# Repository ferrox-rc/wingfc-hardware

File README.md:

# WingFC Hardware Carrier Board

Official hardware carrier board design, schematics, PCB layout, and mechanical CAD for the **WingFC** open-source flight controller ecosystem.

Engineered specifically for sub-250g FPV flying wings, acrobatic wings, and compact autonomous UAVs, this carrier board hosts the **Seeed Studio XIAO nRF52840 Sense Plus** and breaks out all actuation channels, serial links, and power regulation onto an ultra-compact footprint.

---

## 3D Board Visualizations

| Isometric 3D View | Top View | Bottom View |
| :---: | :---: | :---: |
|  |  |  |

---

## Key Hardware Features

- **Standard 25.5 × 25.5 mm Whoop Mounting Pattern:** Fits standard micro-quad and fixed-wing carrier bays with 4× M2 mounting holes (`H1`–`H4`).
- **Ultra-Compact Profile:** Only **32.0 mm wide × 33.2 mm long**, minimizing mass and fuselage cavity requirements.
- **Edge-Mounted North-Facing USB-C Port:**
  - MCU rotated so the USB-C receptacle faces forward into free air.
  - Dedicated $10.0\,\text{mm} \times 0.8\,\text{mm}$ recessed access notch ensures standard USB-C cables plug in flush without mechanical collision.
- **10 Actuator Channels (2 ESCs + 8 Servos):**
  - **6 Primary Channels (`ESC1`, `ESC2`, `S1`..`S4`):** Standard 2.54 mm pitch vertical pin headers (Signal / +5V / GND) nestled directly between lower mounting screws `H3` and `H4`.
  - **4 Auxiliary Channels (`S5`..`S8`):** Compact 1.27 mm pitch horizontal pin headers located in the East bay for advanced airframe functions (flaps, pan/tilt gimbals, landing gear, payload drop).
- **Outward-Facing JST-SH Quick-Connect Sockets:**
  - **RC Receiver (`J_RC`):** 4-pin horizontal JST-SH on the West flank (5V, GND, UARTE0 TX/RX for CRSF/ELRS/iBus).
  - **GPS & Navigation (`J_GPS`):** 6-pin horizontal JST-SH on the East flank (5V, GND, UARTE1 TX/RX for NMEA GPS, TWISPI1 SDA/SCL for external compass).
- **High-Efficiency 5V / 2A Synchronous BEC:**
  - Monolithic Power Systems **MP2315** high-efficiency step-down buck regulator on the bottom layer.
  - Supports 2S to 4S LiPo input voltages (up to 24V).
  - High-current Bourns SRN4018 3.3µH shielded power inductor.
- **Comprehensive Power & Brownout Protection:**
  - **VBAT TVS (`D3`):** Littelfuse SMAJ24A (400W) TVS diode across battery input pads.
  - **+5V TVS (`D4`):** Littelfuse SMAJ5.0A (400W) TVS diode across the servo rail.
  - **Servo Surge Buffer (`C_BULK`):** 100µF 1206 low-ESR ceramic capacitor absorbs motor/servo inductive spikes.
  - **MCU Brownout Hold-Up (`C8` + `D1`):** Diodes Inc B0520W Schottky diode and 22µF 0805 capacitor buffer the MCU 5V rail (`+5V_MCU`) against aerodynamic stall current spikes.
  - **ESC BEC Isolation (`JP1`, `JP2`):** Solder jumpers to disconnect +5V from ESC1 and ESC2 pins, preventing back-feeding into the onboard regulator.
- **Integrated High-Precision Barometer:**
  - Onboard Infineon **DPS310** 24-bit barometric pressure sensor on the secondary I2C bus (`TWISPI1`).
  - Enables sub-meter altitude hold and autonomous vertical Kalman filtering.
- **Antenna Keepout Zone:**
  - Complete copper-free zone across all 4 layers under the South antenna portion of the XIAO module.
- **Breakout & Testability:**
  - SWD test pads (`TP1`..`TP5`): SWCLK, SWDIO, RST, GND, 3V3.
  - Spare GPIO breakout pads (`TP6`..`TP8`): D17, D18, D19.
  - 11:1 precision resistor divider (100kΩ / 10kΩ + 100nF filtering) connected to SAADC `AIN7` (`D16` / `P0.31`) for LiPo pack telemetry.

---

## Pinout & Electrical Allocation

| Header / Pin | Label | nRF52840 Pin | Peripheral | Function |
| :--- | :--- | :--- | :--- | :--- |
| **ESC 1** | `ESC1` | `P0.02` (`D0`) | `PWM0` Ch 0 | Motor 1 (DShot / PWM) |
| **ESC 2** | `ESC2` | `P0.03` (`D1`) | `PWM0` Ch 1 | Motor 2 / Differential Thrust |
| **Servo 1** | `S1` | `P0.04` (`D2`) | `PWM1` Ch 0 | Elevon Left / Aileron |
| **Servo 2** | `S2` | `P0.05` (`D3`) | `PWM1` Ch 1 | Elevon Right / Elevator |
| **Servo 3** | `S3` | `P0.28` (`D4`) | `PWM1` Ch 2 | Rudder / V-Tail |
| **Servo 4** | `S4` | `P0.29` (`D5`) | `PWM1` Ch 3 | Flap Left / Aux |
| **Servo 5** | `S5` | `P0.17` (`D11`)| `PWM2` Ch 0 | Aux / Pan Servo |
| **Servo 6** | `S6` | `P0.18` (`D12`)| `PWM2` Ch 1 | Flap Right / Tilt Servo |
| **Servo 7** | `S7` | `P0.19` (`D13`)| `PWM2` Ch 2 | Aux / Gear Retract |
| **Servo 8** | `S8` | `P0.20` (`D14`)| `PWM2` Ch 3 | Payload Drop / Aux |
| **RC Connector** | `J_RC` | `P1.11` / `P1.12` | `UARTE0` | CRSF / ELRS @ 420k or iBus @ 115.2k |
| **GPS Serial** | `J_GPS` | `P0.09` / `P0.10` | `UARTE1` | NMEA GPS @ 115.2k |
| **External I2C**| `J_GPS` | `P0.15` / `P0.16` | `TWISPI1` | QMC5883L Compass / Ext. Sensors |
| **Battery ADC** | `VBAT_SENSE`| `P0.31` (`D16`)| `SAADC` AIN7 | 11:1 LiPo Voltage Sensing |

---

## KiCad Project Structure

The KiCad project is located in [`kicad/`](kicad/):
- `WingFC.kicad_pro`: KiCad project management file.
- `WingFC.kicad_sch`: Master schematic (includes onboard power supply, filtering, and breakout nets).
- `WingFC.kicad_pcb`: 4-layer PCB layout with dedicated power planes and signal routing.
- `build_pcb.py`: Automated layout generator and validation script.
- `footprints/`: Self-contained project footprint libraries.

---

## Compatible Firmware

This carrier board is fully supported by the **WingFC-rs** bare-metal Rust flight controller firmware:
👉 **[ferrox-rc/wingfc-rs](https://github.com/ferrox-rc/wingfc-rs)**

---

## License

Hardware design files, schematics, PCB layouts, and documentation are licensed under the [MIT License](LICENSE).

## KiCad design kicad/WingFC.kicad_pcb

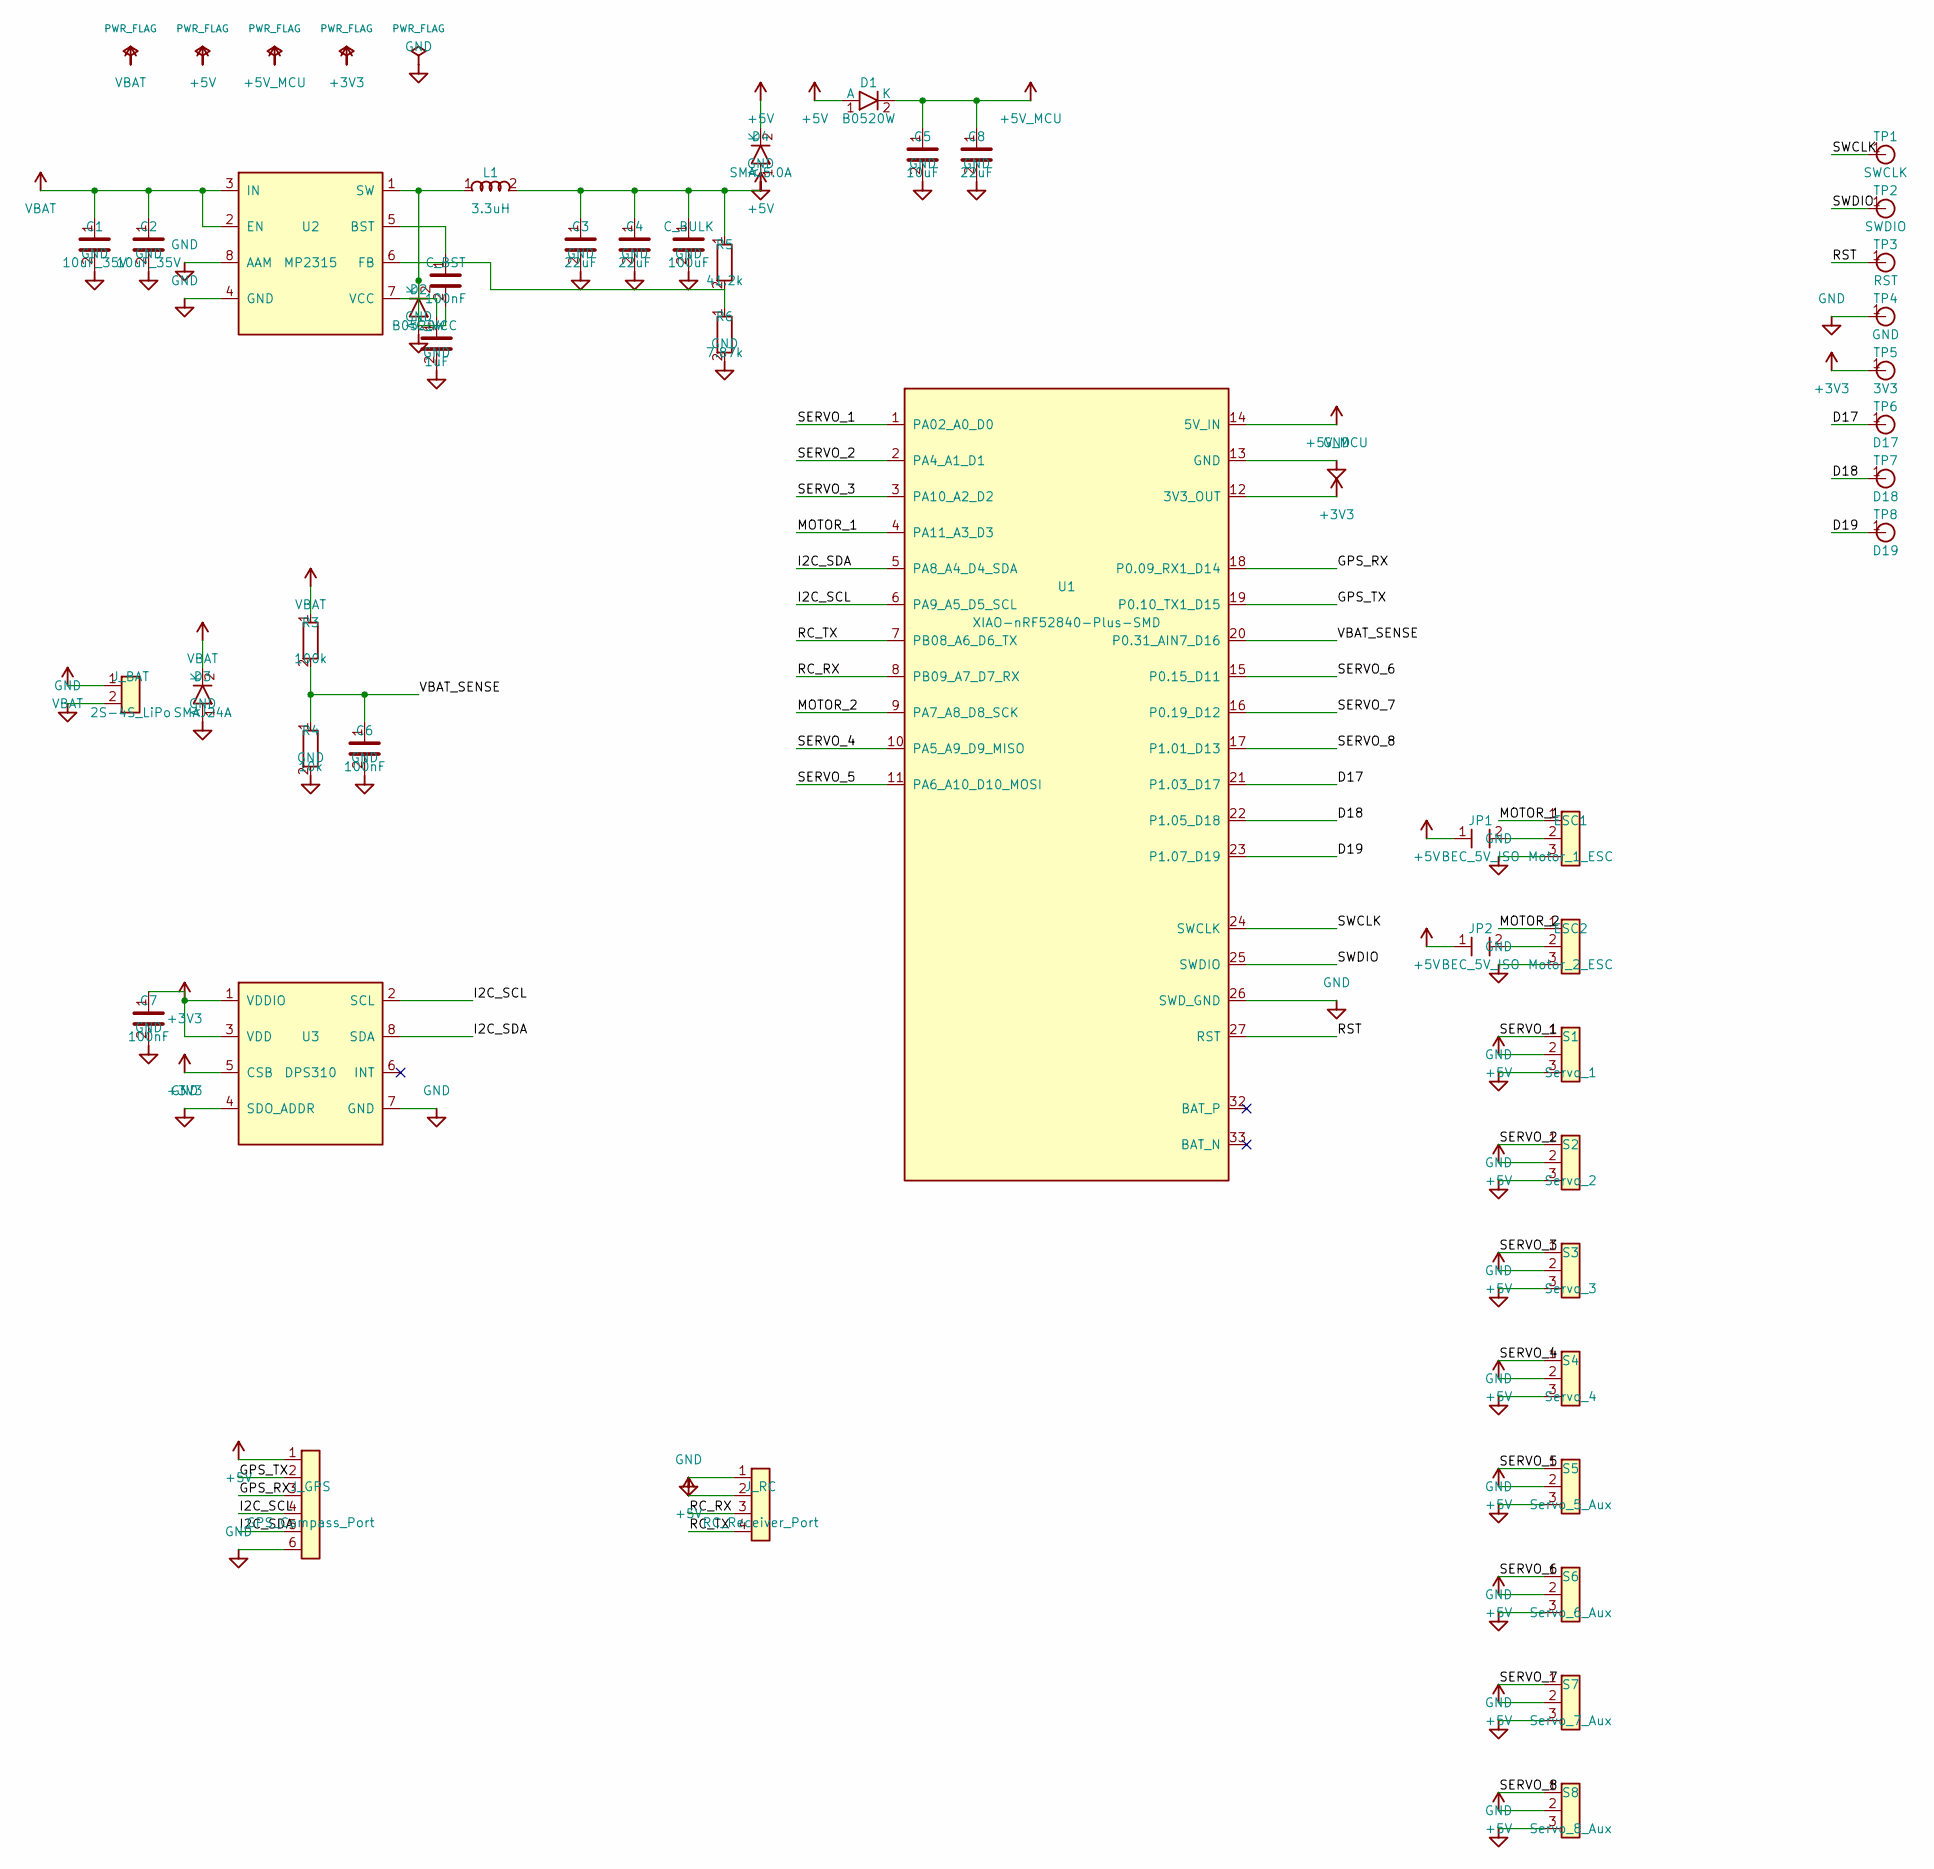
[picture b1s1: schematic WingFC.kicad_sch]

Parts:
C1, C2: 10uF_35V; C_0805_2012Metric
C3, C4, C8: 22uF; C_0805_2012Metric
C5: 10uF; C_0805_2012Metric
C6, C7: 100nF; C_0603_1608Metric
C_BST: 100nF; C_0603_1608Metric
C_BULK: 100uF; C_1206_3216Metric
C_VCC: 1uF; C_0603_1608Metric
D1, D2: B0520W; D_SOD-123
D3: SMAJ24A; D_SMA
D4: SMAJ5.0A; D_SMA
ESC1: Motor_1_ESC; PinHeader_1x03_P2.54mm_Vertical
ESC2: Motor_2_ESC; PinHeader_1x03_P2.54mm_Vertical
JP1, JP2: BEC_5V_ISO; SolderJumper-2_P1.3mm_Open_RoundedPad1.0x1.5mm
J_BAT: 2S-4S_LiPo; SolderWire-0.75sqmm_1x02_P4.8mm_D1.2mm_OD2.3mm
J_GPS: GPS_Compass_Port; JST_SH_SM06B-SRSS-TB_1x06-1MP_P1.00mm_Horizontal
J_RC: RC_Receiver_Port; JST_SH_SM04B-SRSS-TB_1x04-1MP_P1.00mm_Horizontal
L1: 3.3uH; L_Bourns_SRN4018
R3: 100k; R_0603_1608Metric
R4: 10k; R_0603_1608Metric
R5: 41.2k; R_0603_1608Metric
R6: 7.87k; R_0603_1608Metric
S1: Servo_1; PinHeader_1x03_P2.54mm_Vertical
S2: Servo_2; PinHeader_1x03_P2.54mm_Vertical
S3: Servo_3; PinHeader_1x03_P2.54mm_Vertical
S4: Servo_4; PinHeader_1x03_P2.54mm_Vertical
S5: Servo_5_Aux; PinHeader_1x03_P1.27mm_Vertical
S6: Servo_6_Aux; PinHeader_1x03_P1.27mm_Vertical
S7: Servo_7_Aux; PinHeader_1x03_P1.27mm_Vertical
S8: Servo_8_Aux; PinHeader_1x03_P1.27mm_Vertical
TP1: SWCLK; TestPoint_Pad_D1.5mm
TP2: SWDIO; TestPoint_Pad_D1.5mm
TP3: RST; TestPoint_Pad_D1.5mm
TP4: GND; TestPoint_Pad_D1.5mm
TP5: 3V3; TestPoint_Pad_D1.5mm
TP6: D17; TestPoint_Pad_D1.5mm
TP7: D18; TestPoint_Pad_D1.5mm
TP8: D19; TestPoint_Pad_D1.5mm
U1: XIAO-nRF52840-Plus-SMD
U2: MP2315; TSOT-23-8
U3: DPS310; Infineon_PG-VLGA-8-1_2.0x2.5mm_P0.65mm

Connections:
+3V3: C7.1, TP5.1, U1.12 (3V3_OUT), U3.1 (VDDIO), U3.3 (VDD), U3.5 (CSB)
+5V: C3.1, C4.1, C_BULK.1, D1.1 (A), D4.2 (K), JP1.1, JP2.1, J_GPS.1, J_RC.2, L1.2, R5.1, S1.2, S2.2, S3.2, S4.2, S5.2, S6.2, S7.2, S8.2
+5V_MCU: C5.1, C8.1, D1.2 (K), U1.14 (5V_IN)
/D17: TP6.1, U1.21 (P1.03_D17)
/D18: TP7.1, U1.22 (P1.05_D18)
/D19: TP8.1, U1.23 (P1.07_D19)
/GPS_RX: J_GPS.3, U1.18 (P0.09_RX1_D14)
/GPS_TX: J_GPS.2, U1.19 (P0.10_TX1_D15)
/I2C_SCL: J_GPS.4, U1.6 (PA9_A5_D5_SCL), U3.2 (SCL)
/I2C_SDA: J_GPS.5, U1.5 (PA8_A4_D4_SDA), U3.8 (SDA)
/MOTOR_1: ESC1.1, U1.4 (PA11_A3_D3)
/MOTOR_2: ESC2.1, U1.9 (PA7_A8_D8_SCK)
/RC_RX: J_RC.3, U1.8 (PB09_A7_D7_RX)
/RC_TX: J_RC.4, U1.7 (PB08_A6_D6_TX)
/RST: TP3.1, U1.27 (RST)
/SERVO_1: S1.1, U1.1 (PA02_A0_D0)
/SERVO_2: S2.1, U1.2 (PA4_A1_D1)
/SERVO_3: S3.1, U1.3 (PA10_A2_D2)
/SERVO_4: S4.1, U1.10 (PA5_A9_D9_MISO)
/SERVO_5: S5.1, U1.11 (PA6_A10_D10_MOSI)
/SERVO_6: S6.1, U1.15 (P0.15_D11)
/SERVO_7: S7.1, U1.16 (P0.19_D12)
/SERVO_8: S8.1, U1.17 (P1.01_D13)
/SWCLK: TP1.1, U1.24 (SWCLK)
/SWDIO: TP2.1, U1.25 (SWDIO)
/VBAT_SENSE: C6.1, R3.2, R4.1, U1.20 (P0.31_AIN7_D16)
GND: C1.2, C2.2, C3.2, C4.2, C5.2, C6.2, C7.2, C8.2, C_BULK.2, C_VCC.2, D2.1 (A), D3.1 (A), D4.1 (A), ESC1.3, ESC2.3, J_BAT.2, J_GPS.6, J_RC.1, R4.2, R6.2, S1.3, S2.3, S3.3, S4.3, S5.3, S6.3, S7.3, S8.3, TP4.1, U1.13 (GND), U1.26 (SWD_GND), U2.4 (GND), U2.8 (AAM), U3.4 (SDO_ADDR), U3.7 (GND)
unnamed: C_BST.2, D2.2 (K), L1.1, U2.1 (SW)
unnamed: ESC1.2, JP1.2
unnamed: ESC2.2, JP2.2
unnamed: C_BST.1, U2.5 (BST)
unnamed: R5.2, R6.1, U2.6 (FB)
unnamed: C_VCC.1, U2.7 (VCC)
VBAT: C1.1, C2.1, D3.2 (K), J_BAT.1, R3.1, U2.2 (EN), U2.3 (IN)

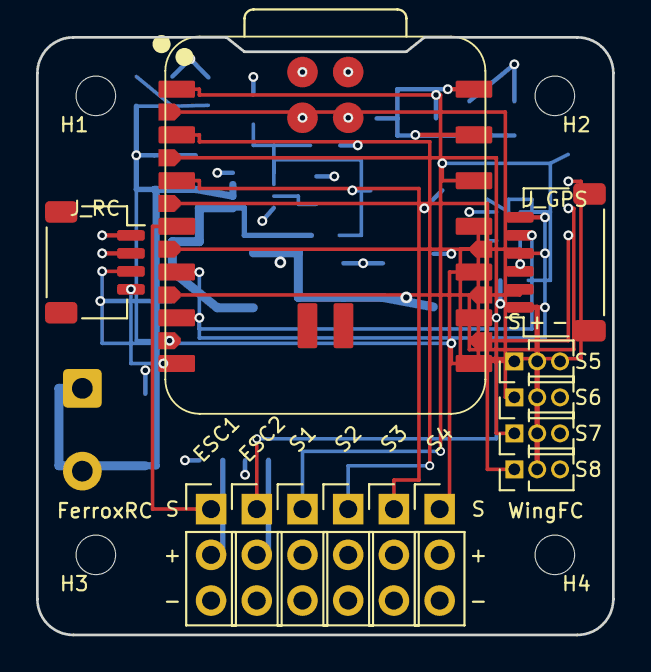
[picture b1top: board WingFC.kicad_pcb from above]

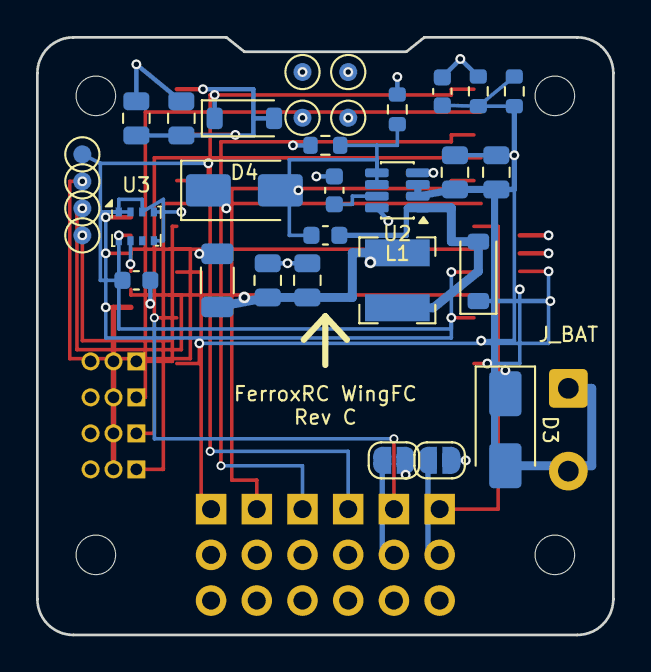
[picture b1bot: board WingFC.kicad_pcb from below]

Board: 4 copper layers, 32.0 x 33.2 mm, 50 parts (33 on the bottom side), 34 nets.

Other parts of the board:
H1, H2, H3, H4: MountingHole_2.2mm_M2

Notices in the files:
README.md:
License: MIT
